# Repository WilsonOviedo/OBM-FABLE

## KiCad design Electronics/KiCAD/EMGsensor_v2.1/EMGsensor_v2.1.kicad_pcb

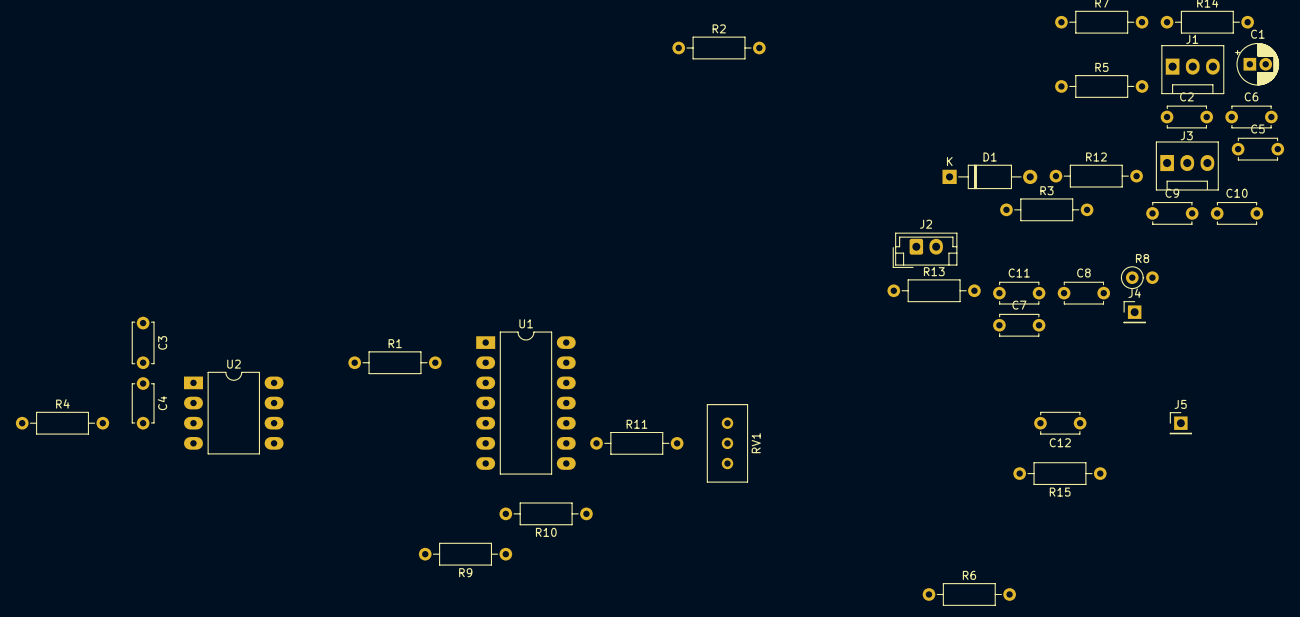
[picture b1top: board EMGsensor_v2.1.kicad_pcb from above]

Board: 2 copper layers, 36 parts (0 on the bottom side), 23 nets, no tracks yet.

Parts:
C1: 47uF; CP_Radial_D5.0mm_P2.00mm
C2, C6: 100nF; C_Disc_D4.7mm_W2.5mm_P5.00mm
C3: 1nF; C_Disc_D5.0mm_W2.5mm_P5.00mm
C4: 1nF; C_Disc_D4.7mm_W2.5mm_P5.00mm
C5: 10nF; C_Disc_D4.7mm_W2.5mm_P5.00mm
C7, C9, C10, C12: 33nF; C_Disc_D4.7mm_W2.5mm_P5.00mm
C8, C11: 3.9nF; C_Disc_D4.7mm_W2.5mm_P5.00mm
D1: D_Schottky; D_A-405_P10.16mm_Horizontal
J1, J3: Conn_01x03_Male; FanPinHeader_1x03_P2.54mm_Vertical
J2: Conn_01x02_Male; JST_EH_B2B-EH-A_1x02_P2.50mm_Vertical
J4: SHIFT; PinHeader_1x01_P2.54mm_Vertical
J5: NO_SHIFT; PinHeader_1x01_P2.54mm_Vertical
R1, R2, R11: 22k; R_Axial_DIN0207_L6.3mm_D2.5mm_P10.16mm_Horizontal
R3, R4: 3.9k; R_Axial_DIN0207_L6.3mm_D2.5mm_P10.16mm_Horizontal
R5: 2.7k; R_Axial_DIN0207_L6.3mm_D2.5mm_P10.16mm_Horizontal
R6, R9, R12, R15: 330k; R_Axial_DIN0207_L6.3mm_D2.5mm_P10.16mm_Horizontal
R7, R10, R13: 10k; R_Axial_DIN0207_L6.3mm_D2.5mm_P10.16mm_Horizontal
R8: 150k; R_Axial_DIN0207_L6.3mm_D2.5mm_P2.54mm_Vertical
R14: 150k; R_Axial_DIN0207_L6.3mm_D2.5mm_P10.16mm_Horizontal
RV1: 100k; Potentiometer_Bourns_3296W_Vertical
U1: OPA4234P; DIP-14_W10.16mm_LongPads
U2: AD623; DIP-8_W10.16mm_LongPads

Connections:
+VDC: D1.2, J2.1
GND: C1.2, C2.2, C3.2, C4.1, C6.2, J1.1, J1.2, J1.3, J2.2, J3.2, R2.2, R6.2, R9.2, R12.2, R15.2, U1.11, U2.4
unnamed: C1.1, C2.1, R1.2, R2.1, U1.2
unnamed: C3.1, C5.1, R3.2, U2.2
unnamed: C4.2, C5.2, R4.2, U2.3
unnamed: C7.1, R6.1, R7.2
unnamed: C7.2, U2.6
unnamed: C8.1, C9.2, R8.1, U1.7
unnamed: C8.2, R7.1, R8.2, U1.6
unnamed: C9.1, R9.1, R10.2
unnamed: C10.1, R12.1, R13.2
unnamed: C10.2, RV1.1, U1.8
unnamed: C11.1, C12.2, J4.1, R14.1, U1.14
unnamed: C11.2, R13.1, R14.2, U1.13
unnamed: C12.1, J5.1, R15.1
unnamed: J3.1, R3.1
unnamed: J3.3, R4.1
unnamed: R5.1, U2.1
unnamed: R5.2, U2.8
unnamed: R10.1, R11.1, U1.9
unnamed: R11.2, RV1.2
VCC: C6.1, D1.1, R1.1, U1.4, U2.7
VMEM: U1.1, U1.3, U1.5, U1.10, U1.12, U2.5

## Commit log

2019-06-10 Create KiCAD EMGsensor v2.1 schematic in KiCAD
2019-06-10 Schematic finish, add gitignore
2019-06-11 Create PCB board
